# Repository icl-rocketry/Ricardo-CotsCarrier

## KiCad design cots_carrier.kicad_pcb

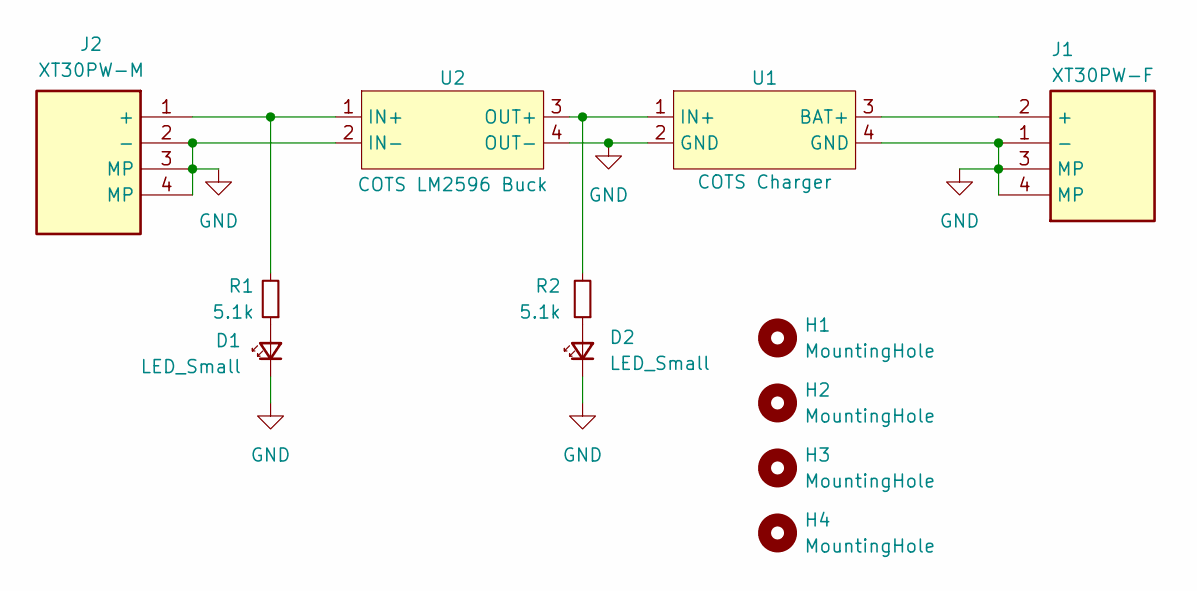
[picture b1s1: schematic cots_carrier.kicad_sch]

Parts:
D1, D2: LED_Small; LED_0603_1608Metric
H1, H2, H3, H4: MountingHole; MountingHole_3.2mm_M3
J1: XT30PW-F; XT30PWF; Manufacturer_Part_Number XT30PW-F
J2: XT30PW-M; XT30PWM; Manufacturer_Part_Number XT30PW-M
R1, R2: 5.1k; R_0603_1608Metric
U1: COTS Charger; DDTCCRUB_COTS_Charger
U2: COTS LM2596 Buck; LM2596_COTS_Buck

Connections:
GND: D1.1 (K), D2.1 (K), J1.1 (-), J1.3 (MP), J1.4 (MP), J2.2 (-), J2.3 (MP), J2.4 (MP), U1.2 (GND), U1.4 (GND), U2.2 (IN-), U2.4 (OUT-)
unnamed: D1.2 (A), R1.1
unnamed: D2.2 (A), R2.1
unnamed: J1.2 (+), U1.3 (BAT+)
unnamed: J2.1 (+), R1.2, U2.1 (IN+)
unnamed: R2.2, U1.1 (IN+), U2.3 (OUT+)

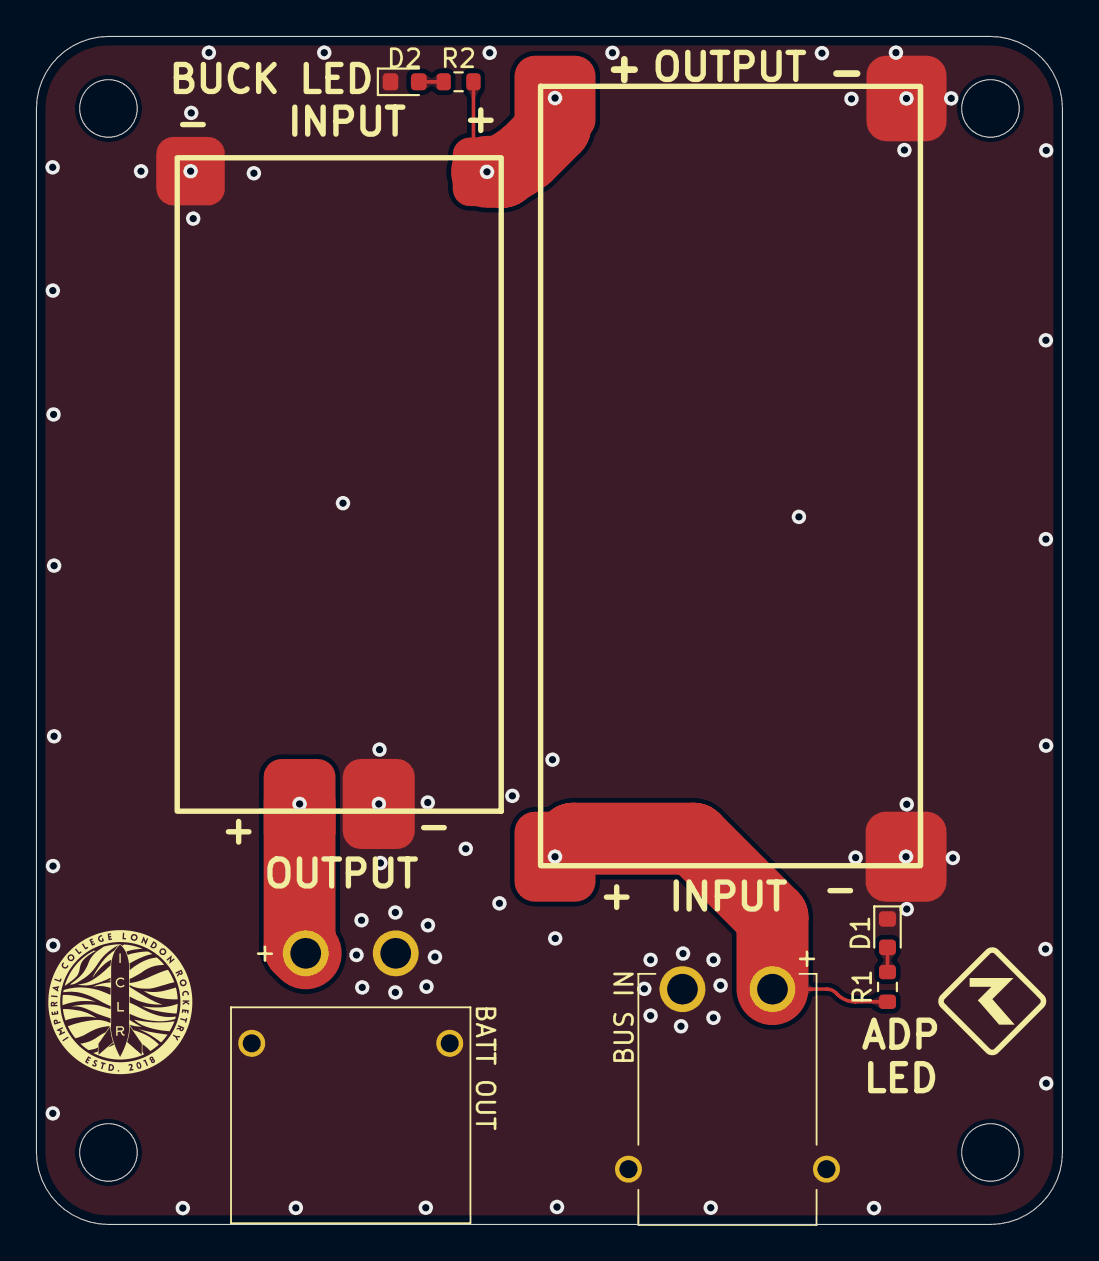
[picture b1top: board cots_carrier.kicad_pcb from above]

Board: 2 copper layers, 57.0 x 66.0 mm, 12 parts (0 on the bottom side), 6 nets.

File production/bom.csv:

Designator,Footprint,Quantity,Value,LCSC Part #
"D1, D2",0603,2,LED_Small,
J1,XT30PWF,1,XT30PW-F,
J2,XT30PWM,1,XT30PW-M,
"R1, R2",0603,2,5.1k,
U1,DDTCCRUB_COTS_Charger,1,COTS Charger,
U2,LM2596_COTS_Buck,1,COTS LM2596 Buck,

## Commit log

2024-07-31 Added cots carrier
2024-07-31 Prod files
2024-08-05 aircraft carrier silk screen
